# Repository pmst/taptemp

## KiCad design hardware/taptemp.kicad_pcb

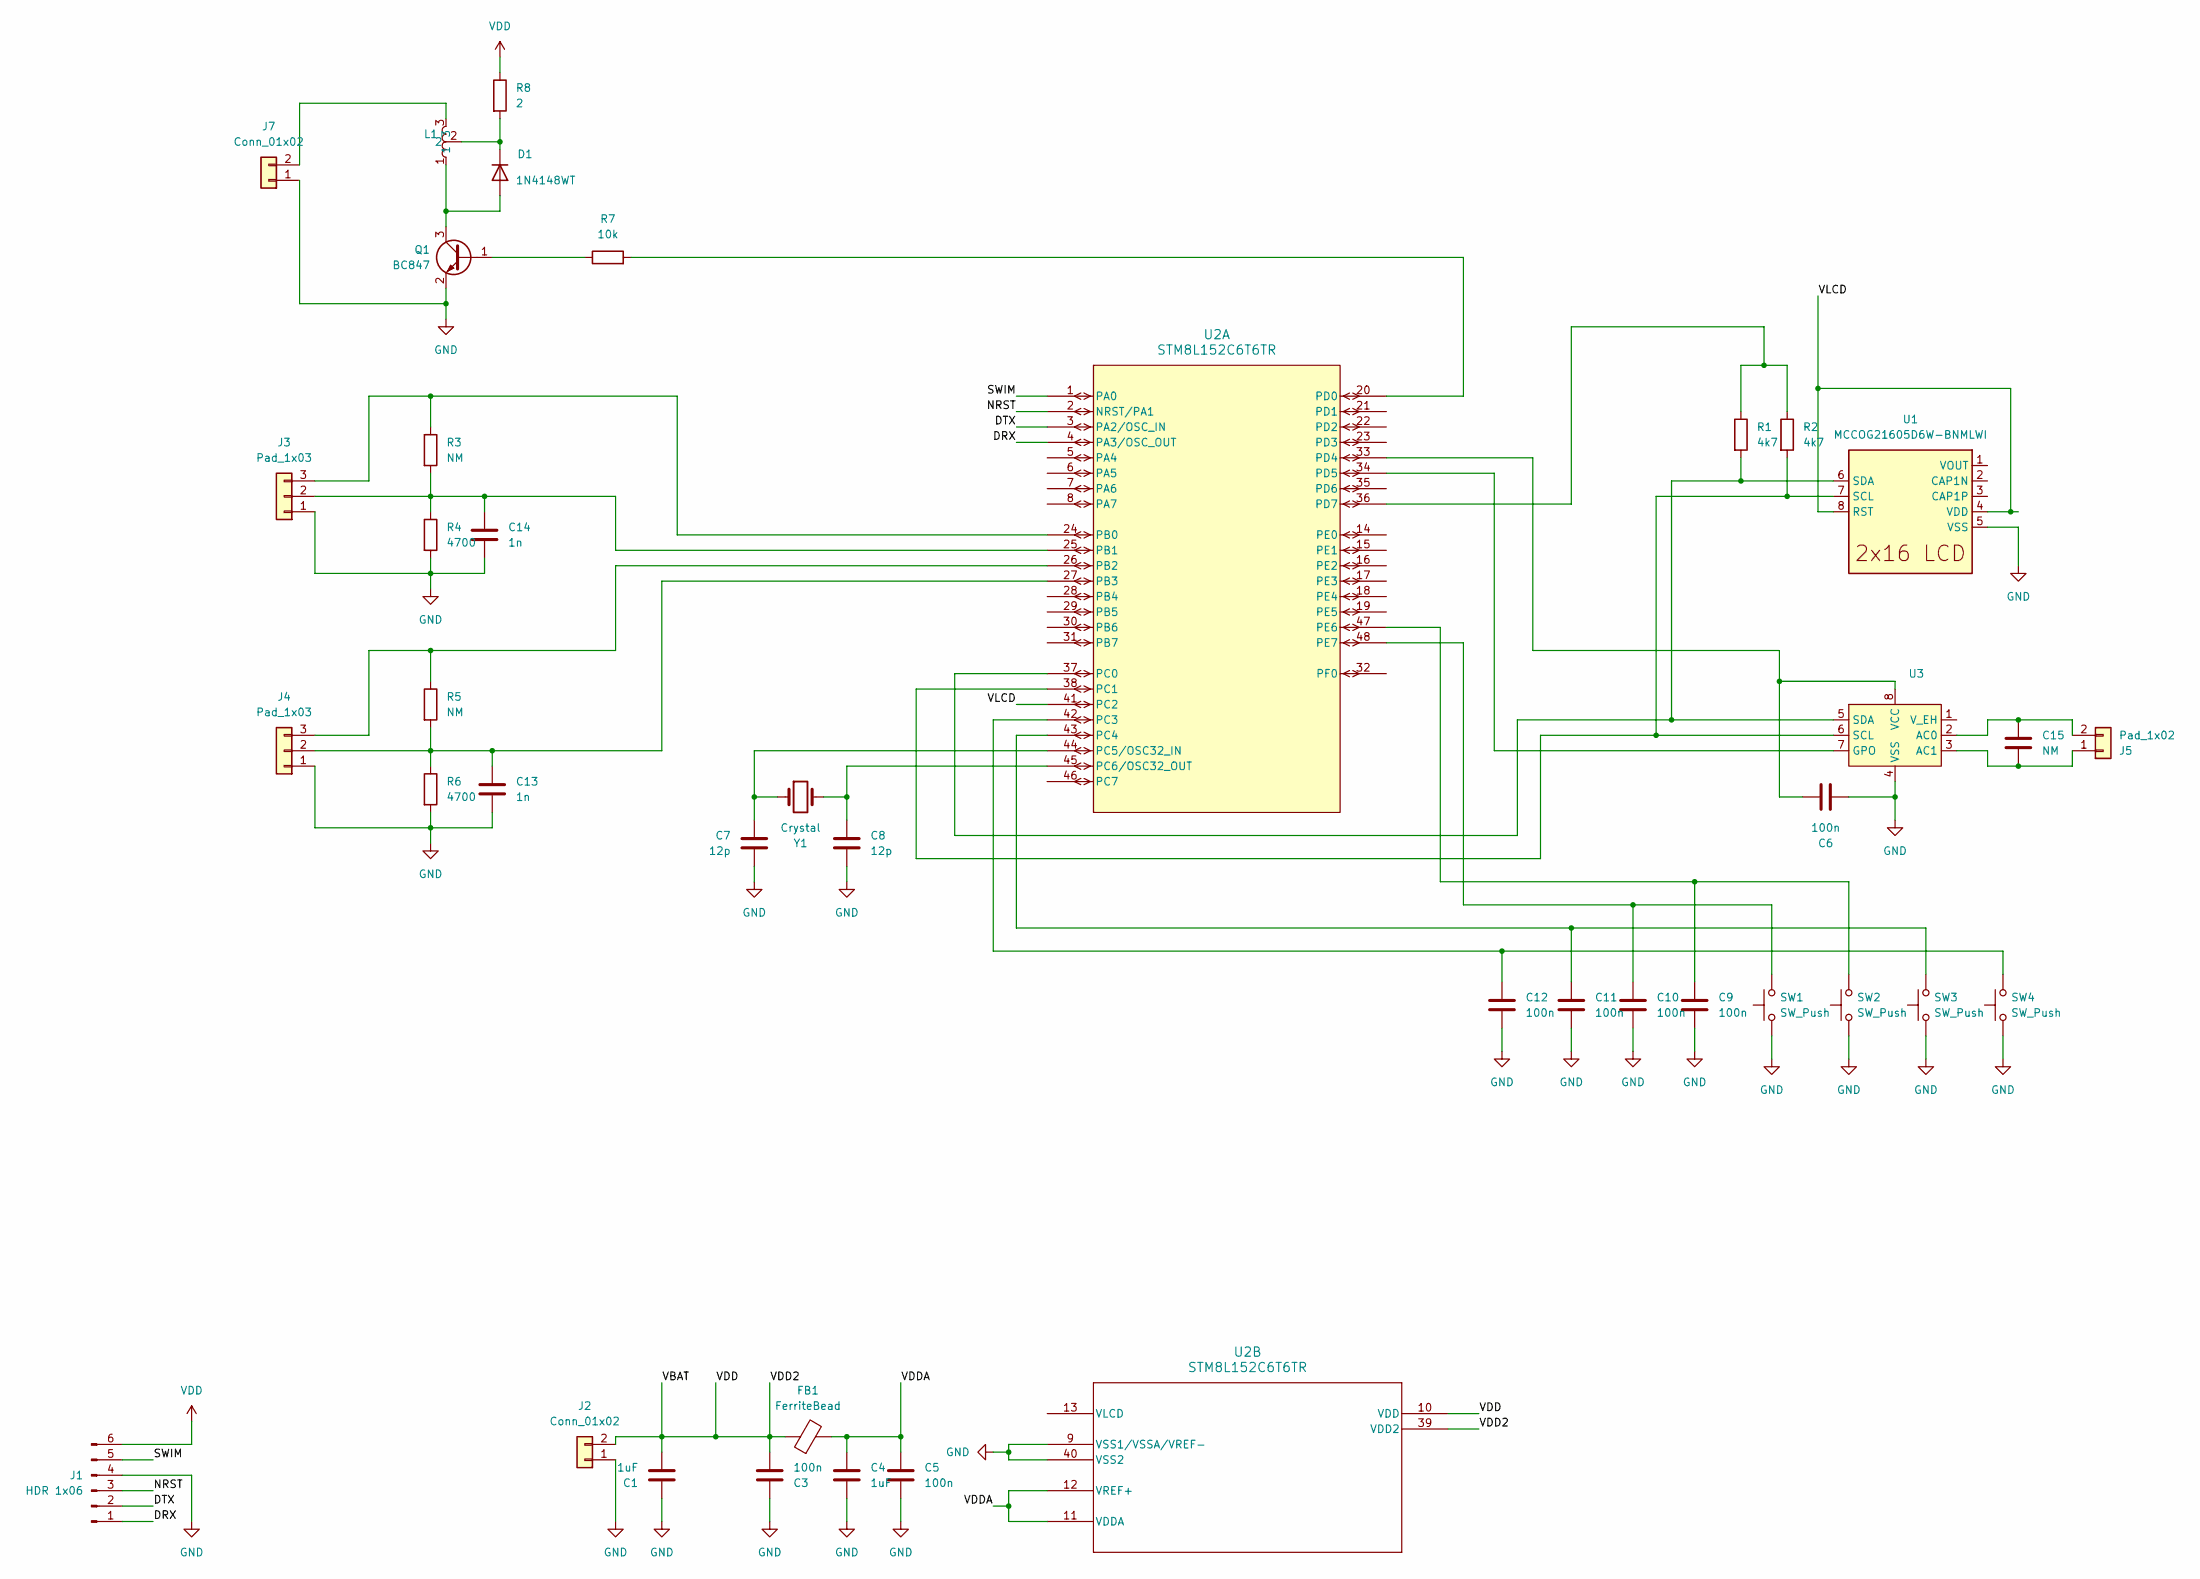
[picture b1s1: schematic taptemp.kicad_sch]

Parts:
C1, C4: 1uF; C_0603_1608Metric_Pad1.08x0.95mm_HandSolder
C3, C5, C9, C10, C11, C12: 100n; C_0603_1608Metric_Pad1.08x0.95mm_HandSolder
C6: 100n; C_0805_2012Metric_Pad1.18x1.45mm_HandSolder
C7, C8: 12p; C_0603_1608Metric_Pad1.08x0.95mm_HandSolder
C13, C14: 1n; C_0603_1608Metric_Pad1.08x0.95mm_HandSolder
C15: NM; C_0603_1608Metric_Pad1.08x0.95mm_HandSolder
D1: 1N4148WT; D_SOD-523
FB1: FerriteBead; L_0603_1608Metric_Pad1.05x0.95mm_HandSolder
J1: HDR 1x06; PinHeader_1x06_P2.54mm_Horizontal
J2: Conn_01x02; JST_PH_S2B-PH-SM4-TB_1x02-1MP_P2.00mm_Horizontal
J3, J4: Pad_1x03; Pad1x03
J5: Pad_1x02; Pad1x02
J7: Conn_01x02; Pad1x02
L1: Pad1x03
Q1: BC847; SOT-23
R1, R2: 4k7; R_0603_1608Metric_Pad0.98x0.95mm_HandSolder
R3, R5: NM; R_0603_1608Metric_Pad0.98x0.95mm_HandSolder
R4, R6: 4700; R_0603_1608Metric_Pad0.98x0.95mm_HandSolder
R7: 10k; R_0603_1608Metric_Pad0.98x0.95mm_HandSolder
R8: 2; R_0603_1608Metric_Pad0.98x0.95mm_HandSolder
SW1, SW2, SW3, SW4: SW_Push; SW_Push_1P1T_NO_E-Switch_TL3301NxxxxxG
U1: MCCOG21605D6W-BNMLWI; MCCOG21605D6W
U2: STM8L152C6T6TR; LQFP-48_7x7mm_P0.5mm
U3: SO-8_3.9x4.9mm_P1.27mm
Y1: Crystal; Crystal_SMD_3215-2Pin_3.2x1.5mm

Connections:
/DRX: J1.1, U2.4 (PA3/OSC_OUT)
/DTX: J1.2, U2.3 (PA2/OSC_IN)
/NRST: J1.3, U2.2 (NRST/PA1)
/SWIM: J1.5, U2.1 (PA0)
/VDDA: C4.2, C5.2, FB1.2, U2.11 (VDDA), U2.12 (VREF+)
/VLCD: U1.4 (VDD), U1.8 (RST), U2.41 (PC2)
GND: C1.1, C3.1, C4.1, C5.1, C6.1, C7.1, C8.1, C9.2, C10.2, C11.2, C12.2, C13.2, C14.2, J1.4, J2.1, J3.1, J4.1, J7.1, Q1.2 (E), R4.2, R6.2, SW1.1, SW2.1, SW3.1, SW4.1, U1.5 (VSS), U2.9 (VSS1/VSSA/VREF-), U2.40 (VSS2), U3.4 (VSS)
unnamed: D1.2 (A), L1.1, Q1.3 (C)
unnamed: D1.1 (K), L1.2, R8.2
unnamed: C14.1, J3.2, R3.2, R4.1, U2.25 (PB1)
unnamed: J3.3, R3.1, U2.24 (PB0)
unnamed: C13.1, J4.2, R5.2, R6.1, U2.27 (PB3)
unnamed: J4.3, R5.1, U2.26 (PB2)
unnamed: C15.2, J5.1, U3.3 (AC1)
unnamed: C15.1, J5.2, U3.2 (AC0)
unnamed: J7.2, L1.3
unnamed: Q1.1 (B), R7.1
unnamed: R2.2, U1.7 (SCL), U2.38 (PC1), U3.6 (SCL)
unnamed: R1.2, U1.6 (SDA), U2.37 (PC0), U3.5 (SDA)
unnamed: C12.1, SW4.2, U2.42 (PC3)
unnamed: C11.1, SW3.2, U2.43 (PC4)
unnamed: C7.2, U2.44 (PC5/OSC32_IN), Y1.1
unnamed: C8.2, U2.45 (PC6/OSC32_OUT), Y1.2
unnamed: R7.2, U2.20 (PD0)
unnamed: C6.2, U2.33 (PD4), U3.8 (VCC)
unnamed: U2.34 (PD5), U3.7 (GPO)
unnamed: R1.1, R2.1, U2.36 (PD7)
unnamed: C9.1, SW2.2, U2.47 (PE6)
unnamed: C10.1, SW1.2, U2.48 (PE7)
VDD: C1.2, C3.2, FB1.1, J1.6, J2.2, R8.1, U2.10 (VDD), U2.39 (VDD2)

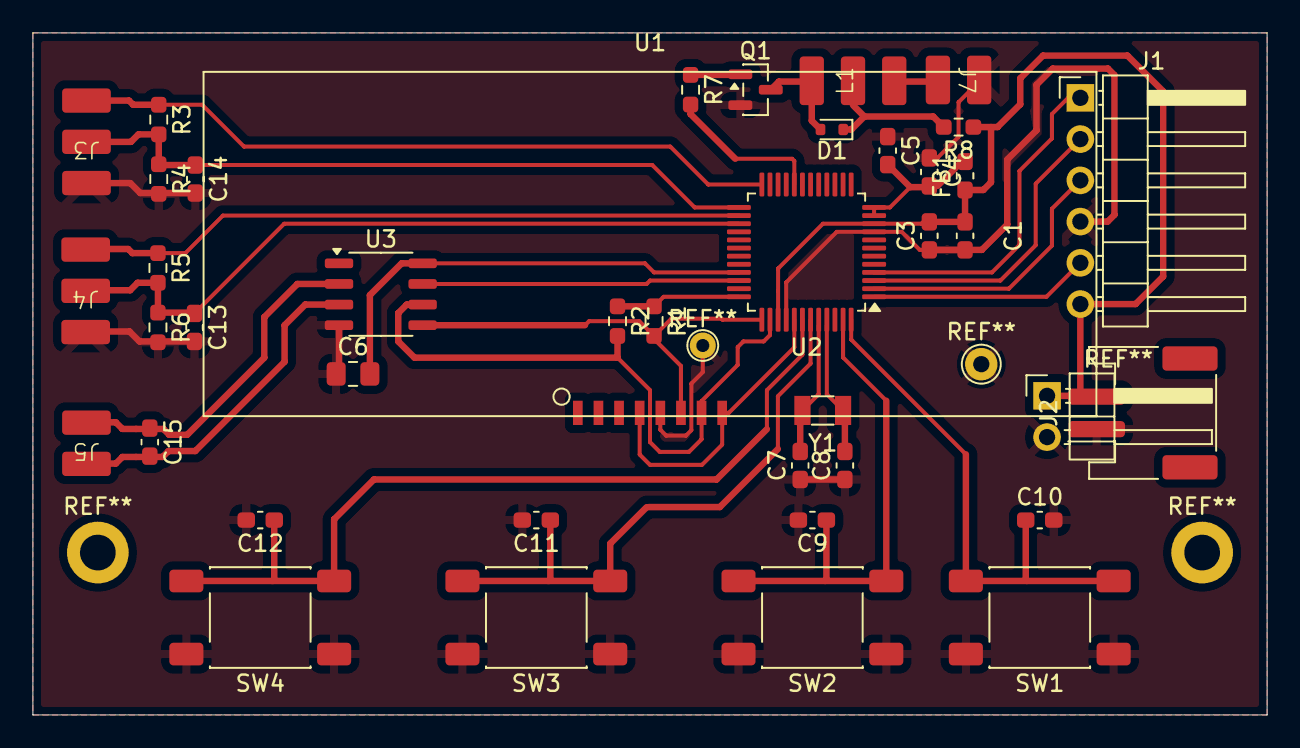
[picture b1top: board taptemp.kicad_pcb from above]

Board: 2 copper layers, 76.0 x 42.0 mm, 40 parts (0 on the bottom side), 30 nets.

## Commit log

2025-11-07 Add initial README.md file
2025-11-23 dev: added hardware folder
2025-12-14 dev: partial version with efm32
2025-12-21 dev: initial design with stm8
2026-03-14 dev: completed routing
